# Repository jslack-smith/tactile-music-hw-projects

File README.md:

# tactile-music-hw-projects
Tactile Music is a project for an electrical engineering design course, ELEC3117, at UNSW.
This repo is for EAGLE project files.

How to use:
* clone this repo into your EAGLE projects folder

Notes:
* Use the DINA4_L (A4, landscape) frame on all sheets
* Use R-US_R0805 for resistors
* Use LEDCHIPLED_0805 for LED's

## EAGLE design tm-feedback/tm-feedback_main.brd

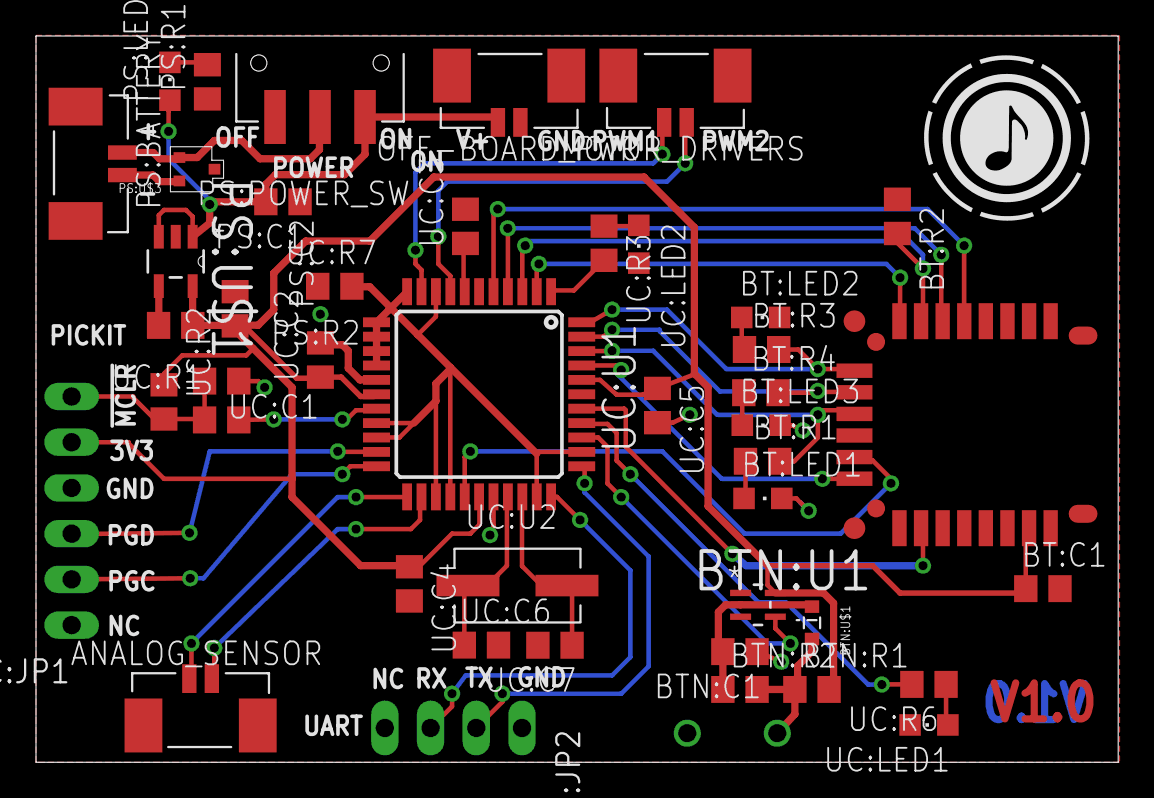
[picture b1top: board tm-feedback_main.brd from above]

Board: 2 copper layers, 60.1 x 40.3 mm, 45 parts (1 on the bottom side), 41 nets.

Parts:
ANALOG_SENSOR: PICOBLADE
BT:C1: 4.7uF; C0805
BT:LED1: YELLOW; CHIPLED_0805
BT:LED2: RED; CHIPLED_0805
BT:LED3: GREEN; CHIPLED_0805
BT:R1, BT:R3, BT:R4: 53.6Ω; R0805
BT:R2: 10kΩ; R0805
BT:U$1: RN4020
BTN:C1: 1uF; C0805
BTN:PAIRING_SW: MC32881_TACTILE; THRU-TACTILE-BTN
BTN:R1: 33k; R0805
BTN:R2: 18k; R0805
BTN:U1: 74AUP1G17GW; SOT65P212X110-5N
BTN:U$1: DB2S308; SOD-523
MOTOR_DRIVERS: PICOBLADE
OFF-BOARD_PWR: PICOBLADE
PS:BATTERY: PICOBLADE
PS:C1, PS:C2: 10uF; C0805
PS:LED1: RED; CHIPLED_0805
PS:POWER_SW: JS102011SAQN
PS:R1: 53.6Ω; R0805
PS:R2: 10k; R0805
PS:U$1: MCP1824T-3302E/OT; SOT95P270X145-5N
PS:U$3: PMF370XN; SOT323(SC-70)
UC:C1: C0805
UC:C2, UC:C4, UC:C5: 0.1uF; C0805
UC:C3: 10uF; C0805
UC:C6, UC:C7: 27pF; C0805
UC:JP1: PICKIT; 1X06/90
UC:JP2: UART_PC; 1X04/90
UC:LED1, UC:LED2: GREEN; CHIPLED_0805
UC:R1: 330Ω; R0805
UC:R2, UC:R7: 10kΩ; R0805
UC:R3, UC:R6: 53.6Ω; R0805
UC:U1: DSPIC33EP512MC504; TQFP44
UC:U2: XTAL_ABLS7M2

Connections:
+3V3: BT:C1.1, BT:U$1.23, BTN:R1.2, BTN:U1.5, PS:C2.2, PS:R2.2, PS:U$1.5, UC:C2.1, UC:C4.1, UC:C5.1, UC:JP1.5, UC:R2.2, UC:U1.17, UC:U1.28, UC:U1.40
BT:N$6: BT:LED2.A, BT:R3.1
BT:N$7: BT:LED3.A, BT:R4.1
BT:N$8: BT:LED1.A, BT:R1.1
BTN:N$1: BTN:PAIRING_SW.P$2, BTN:R1.1, BTN:R2.2, BTN:U$1.2
BTN:N$2: BTN:C1.2, BTN:R2.1, BTN:U1.2, BTN:U$1.1
GND: BT:C1.2, BT:LED1.C, BT:LED2.C, BT:LED3.C, BT:R2.1, BT:U$1.1, BT:U$1.9, BT:U$1.16, BT:U$1.24, BTN:C1.1, BTN:PAIRING_SW.P$1, BTN:U1.3, OFF-BOARD_PWR.1, PS:C1.1, PS:C2.1, PS:R1.1, PS:U$1.2, PS:U$3.3, UC:C1.2, UC:C2.2, UC:C3.2, UC:C4.2, UC:C5.2, UC:C6.2, UC:C7.2, UC:JP1.4, UC:JP2.1, UC:LED1.C, UC:LED2.C, UC:R7.2, UC:U1.6, UC:U1.16, UC:U1.29, UC:U1.39
unnamed: BTN:U1.4, UC:U1.36
unnamed: BT:U$1.14, UC:U1.27
unnamed: OFF-BOARD_PWR.2, PS:C1.2, PS:LED1.A, PS:POWER_SW.1, PS:U$1.1, PS:U$1.3
unnamed: BT:U$1.18, UC:U1.38
unnamed: BT:U$1.5, UC:U1.5
unnamed: BT:U$1.6, UC:U1.4
unnamed: BT:U$1.15, UC:U1.41
unnamed: BT:R2.2, BT:U$1.7, UC:U1.3
unnamed: BT:U$1.8, UC:U1.2
unnamed: BT:R3.2, BT:U$1.10, UC:U1.44
unnamed: BT:R4.2, BT:U$1.11, UC:U1.43
unnamed: BT:R1.2, BT:U$1.12, UC:U1.42
unnamed: ANALOG_SENSOR.1, UC:U1.23
unnamed: ANALOG_SENSOR.2, UC:U1.24
PS:BATT_V+: PS:BATTERY.1, PS:POWER_SW.2, PS:U$3.1
PS:BATT_V-: PS:BATTERY.2, PS:U$3.2
PS:N$3: PS:LED1.C, PS:R1.2
PS:PWRGD: PS:R2.1, PS:U$1.4
PWM_1: MOTOR_DRIVERS.2, UC:U1.10
PWM_2: MOTOR_DRIVERS.1, UC:U1.8
UC:!MCLR: UC:C1.1, UC:JP1.6, UC:R1.1, UC:R2.1
UC:LED1: UC:R6.2, UC:U1.37
UC:LED2: UC:R3.2, UC:U1.1
UC:N$1: UC:R1.2, UC:U1.18
UC:N$3: UC:C3.1, UC:U1.7
UC:N$4: UC:LED2.A, UC:R3.1
UC:N$10: UC:LED1.A, UC:R6.1
UC:OSC1: UC:C6.1, UC:U1.30, UC:U2.1
UC:OSC2: UC:C7.1, UC:U1.31, UC:U2.2
UC:PGC: UC:JP1.2, UC:U1.22
UC:PGD: UC:JP1.3, UC:U1.21
UC:UART2_RX: UC:JP2.3, UC:U1.33
UC:UART2_TX: UC:JP2.2, UC:U1.34
UC:UNUSED: UC:R7.1, UC:U1.9, UC:U1.11, UC:U1.12, UC:U1.13, UC:U1.14, UC:U1.15, UC:U1.19, UC:U1.20, UC:U1.25, UC:U1.26, UC:U1.32, UC:U1.35

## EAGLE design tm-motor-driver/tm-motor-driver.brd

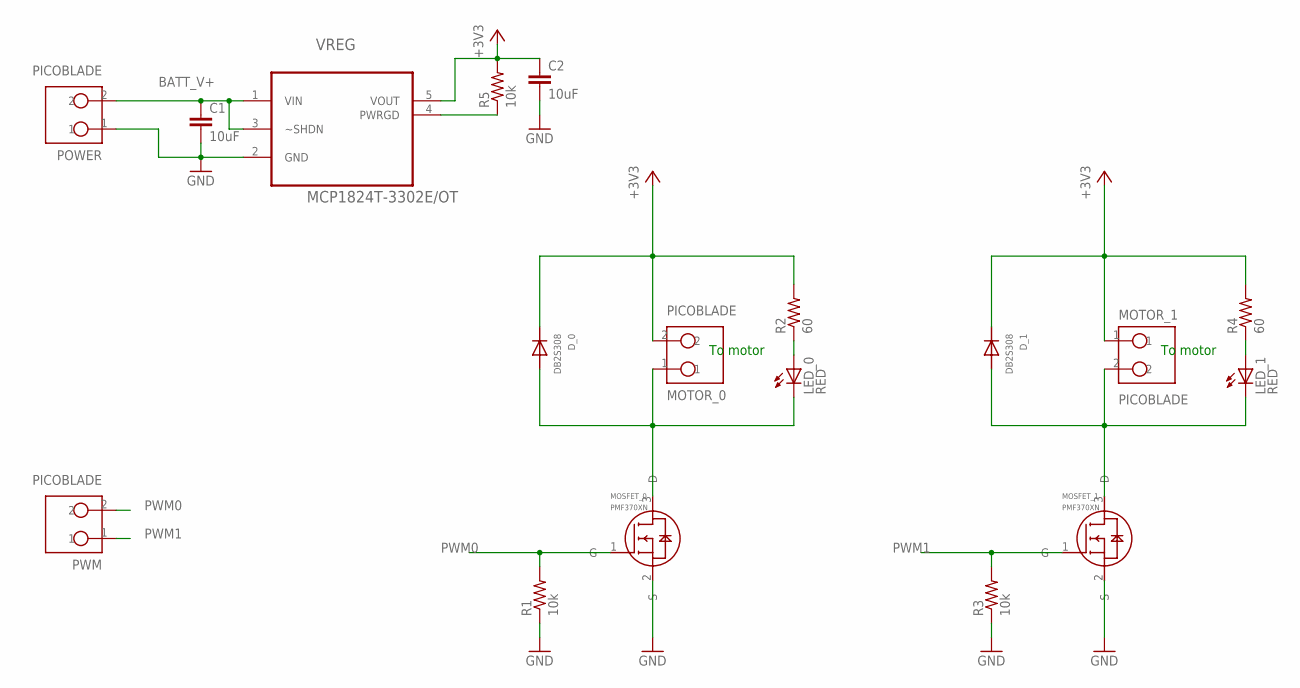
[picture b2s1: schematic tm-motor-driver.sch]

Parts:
C1, C2: 10uF; C0805
D_0, D_1: DB2S308; SOD-523
LED_0, LED_1: RED; CHIPLED_0805
MOSFET_0, MOSFET_1: PMF370XN; SOT323(SC-70)
MOTOR_0, MOTOR_1: PICOBLADE
POWER: PICOBLADE
PWM: PICOBLADE
R1, R3, R5: 10k; R0805
R2, R4: 60; R0805
VREG: MCP1824T-3302E/OT; SOT95P270X145-5N

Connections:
+3V3: C2.1, D_0.1 (CATHODE), D_1.1 (CATHODE), MOTOR_0.2, MOTOR_1.1, R2.2, R4.2, R5.2, VREG.5 (VOUT)
BATT_V+: C1.1, POWER.2, VREG.1 (VIN), VREG.3 (~SHDN)
GND: C1.2, C2.2, MOSFET_0.2 (S), MOSFET_1.2 (S), POWER.1, R1.1, R3.1, VREG.2 (GND)
unnamed: D_1.2 (ANODE), LED_1.C, MOSFET_1.3 (D), MOTOR_1.2
unnamed: D_0.2 (ANODE), LED_0.C, MOSFET_0.3 (D), MOTOR_0.1
unnamed: LED_0.A, R2.1
unnamed: LED_1.A, R4.1
unnamed: R5.1, VREG.4 (PWRGD)
PWM0: MOSFET_0.1 (G), PWM.2, R1.2
PWM1: MOSFET_1.1 (G), PWM.1, R3.2

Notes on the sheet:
To motor

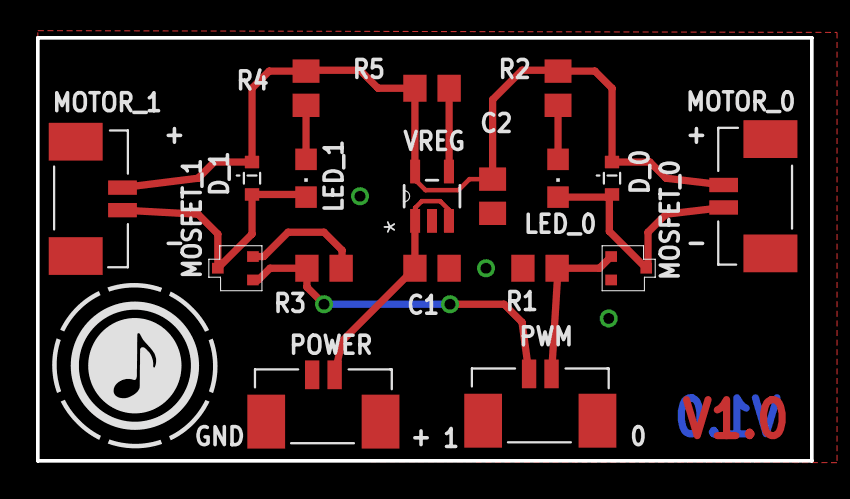
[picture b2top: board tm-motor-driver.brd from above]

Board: 2 copper layers, 43.0 x 23.5 mm, 18 parts (0 on the bottom side), 10 nets.

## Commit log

2016-09-15 Create tm-feedback EAGLE project
2016-09-17 Create some empty modules
2016-09-17 Add note on which frame to use
2016-09-17 Create all modules (empty)
2016-09-17 Add ports to modules (bluetooth, uC) not complete
2016-09-17 Add some intermodule connections
2016-09-18 Add note on which resistor device to use
2016-09-18 Add note on which LED device to use
2016-09-18 Add some components, complete motor driver
2016-09-21 Add headers
2016-09-21 Added gitignore, to ignore backup files
2016-09-21 Deleted backup files
2016-09-21 Add some custom library components to schematics
2016-09-22 Made a start on the bluetooth module
2016-09-22 Completed Bluetooth Module
2016-09-23 First version of motor driver schematic
2016-09-23 Add R on power good
2016-09-23 Add note about input cap size choice
2016-09-23 Remove jumpers, rearrange LED and series resistor for easier layout
2016-09-23 Change header to JST
2016-09-23 Change MOTOR_0 JST connections to make PCB routing easier
2016-09-24 Fixed simple schematic errors, and made some PCB fixes / enhancements
2016-09-24 Fix LED_0 clearance error
2016-09-24 Reduce board size
2016-09-24 Move VREG name
2016-09-24 Added value to bluetooth module decoupling cap
2016-09-24 Generate gerber files
2016-09-24 Added dsPIC into microcontroller schematic
2016-09-24 Regenerate gerber files
2016-09-24 Started on PIC schematic
2016-09-24 Change PS, add button, remove MOTOR_DRIVER
2016-09-24 Add power switch
2016-09-24 Wired most of the board up. Currently have ERC issues.
2016-09-25 Moved Bluetooth Module to rigth place
2016-09-25 Rearrange power
2016-09-25 Unlock
2016-09-25 Fixed and approved ERC errors
2016-09-25 Replaced JST with picoblade
2016-09-25 Update PICOBLADE
2016-09-25 Add tactile
2016-09-25 Resize board with new connectors
2016-09-25 First attempt at board layout for main board
2016-09-25 Arrange PS, rearrange PWM connections for easier layout, rename modules for shorter names (I will try do shorter commits\!)
2016-09-25 Route power supply and button
2016-09-25 More routing
2016-09-25 More layout
2016-09-25 Even more board layout
2016-09-25 Finished board layout
2016-09-26 Fix ground vias
2016-09-26 Fix more ground vias
2016-09-26 Replace PICKIT header with new header
2016-09-26 Replace headers in schematic and board, no design rule errors
2016-09-26 Add labels, icon
2016-09-26 Remove locks
2016-09-29 Changed LEDs to more accurate values
2016-10-05 Fix power supply, shutdown should be connected to Vin not Vout
